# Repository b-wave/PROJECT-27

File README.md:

# PROJECT-27
Which was a Telemetering transmitter from the 1964 era book **103 Simple Transistor Projects**, by Tom Knitel  I grew up with this book and this was one of my bucket-list projects from it. Although I am *not exactly sure* how my pre-teen self planned to send this device aloft.  I do remember trying to build it up with a CB radio crystal and a few random transistors (it never worked) and had some vague idea of 20 or so toy helium balloons in a laundry bag! Informaton from this transmitter is not sent digitally from this device either.  The RF is AM modulated and the frequency of the modulation is controlled by a thermistor.  Of course, this would need to be calibrated to make any sense of the data. 

For more details on my check out my site: (https://brainwave57.blogspot.com/2022/11/project-27-part-1.html)

103 Projects!

I created two versions, MKI and MKIII are functional. The MK1 is pretty much a copy of the original version. The Mk3 may actually be legal to operate as a telemetering device on the current 27-MHz band. The MK3 is a modern version that also features the same simple Temperature-to-Frequency converter it also now includes a way to include altitude information encoded in the length of the tone burst (Pulse modulated) and even a bright LED beacon.  I thought I had some of the original Ge Transistors, but it turned out they were really old-style Si devices. I found sources for the original transistors online but at a cost that did not make it practical to try or even risk these antique transistors to this experiment... Even buying the Over Tone crystals is costly. I did find a solution for both.  

They are built without any Germanium or PNP transistors. 

The files here are "modern" versions of the **#27 Telemetering Transmitter**. Basically, the first version was a simple crystal oscillator and a multivibrator circuit - just like the original. The crystal was taken from a toy "27MHZ" remote controller. It turns out the frequency is in the ISM telemetry part of that band. The original project #27 goes into detail about the FCC requirements, in force in 1964. He even recommends the transmitter is inspected by a certified person to comply with the then requirements. I did a quick search of the FCC rules and found the mentioned sections are not even in existence. I did see the current requirements have differences are that more power is apparently now allowed - but - there is now a limit now on the length of time a "tone" can be transmitted. The original and MK1 transmit continuously so they would definitely not be legal. But of course, none of these transmitters are FCC type accepted for manufacture but for experimental purposes on the ISM band it should be OK.

Telemetering Tranmiter Version MK1 3D View

That's why the new Mk3 version.  It attempts to limit the time that the tone is transmitted and clean up the output to hopefully comply with the rules.  The original seems to rely on low power and the antenna length to limit the spurious emissions surely caused by a 3rd overtone crystal oscillator.  The timing circuit was implemented as another two-transistor multivibrator. Since it originally started life as a "Flashing beacon" in the same book -- I also added a high efficiency LED that produces a bright strobe beacon as well so it can be tracked and possibly help find it.  Since the strobes timing was arbitrarily set, I realized that that could be, in fact, controlled and a second channel of information could be transmitted by this pulse length.  I then constructed a 1960's technology version of an altimeter that is a simple sealed tube of air with a plunger attached to a slide potentiometer. I will add details of this device later. (Mk2 was a never completed high(er) power version)

Telemetering Tranmitter Version MK3 (Top 3D View)

The original was intended to powered only by 1.5V AA cell.  Three volts would actually be OK for FCC power output requirements. I think a modern LiPo would probably survive the extreme cold a balloon-borne sonde would encounter. There is now plenty of room for two cells as shown on the bottom view. Of course, weight is a prime consideration for balloon payloads as well so LiPo may be best.  

Tranmitter Version MK3 (Bottom 3D View)

I doubt if this thing ever did fly on a balloon to or will my version but it was a fun pandemic project just to see it work. 

#Circuit boards are availble on:

MKI  Board: https://oshpark.com/shared_projects/9dS7OwyD

MKII Board:  **Never Finished** 

MKIII Board: https://oshpark.com/shared_projects/CLHAeEab

Cheers!

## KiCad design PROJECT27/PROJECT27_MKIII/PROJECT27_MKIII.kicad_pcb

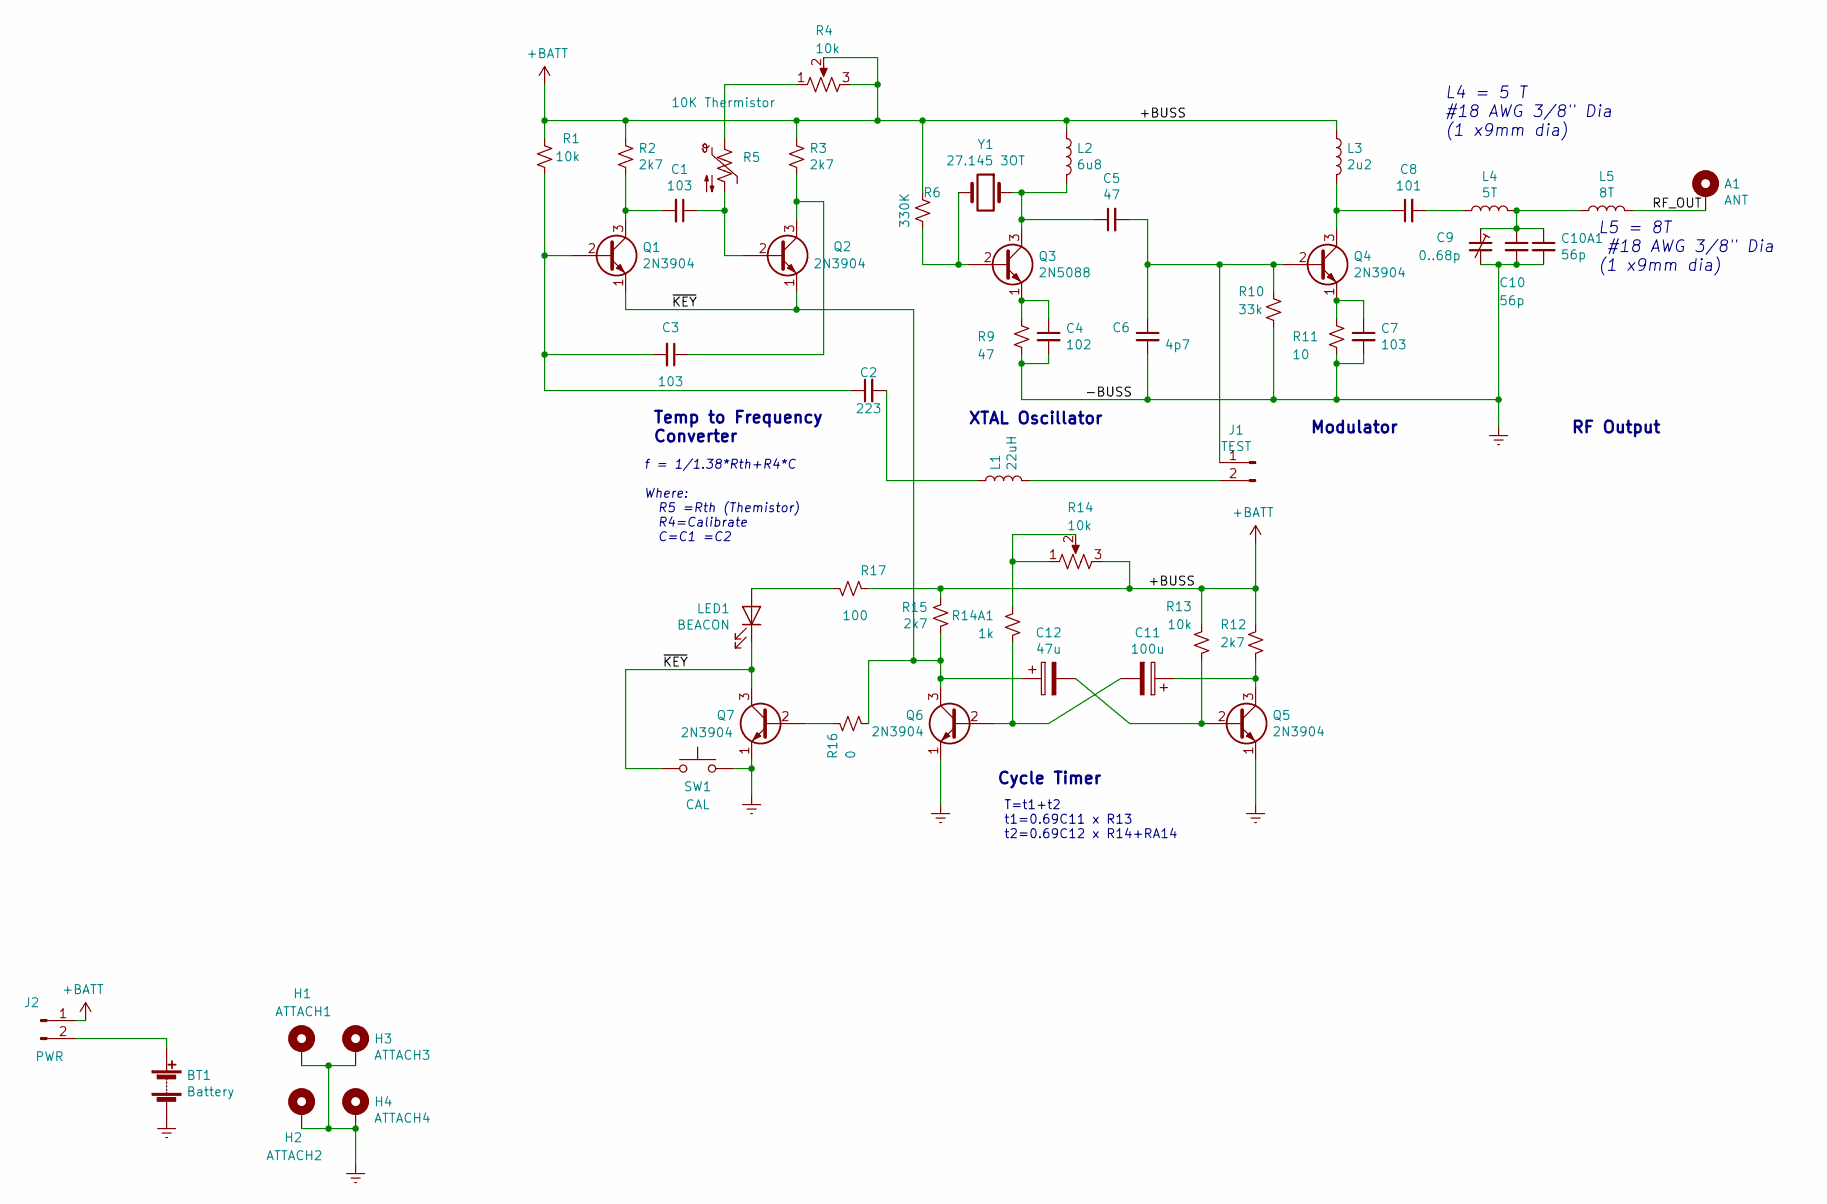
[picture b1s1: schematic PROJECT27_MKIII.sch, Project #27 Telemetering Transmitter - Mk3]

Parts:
A1: ANT; Hole_100_75
BT1: Battery; BatteryHolder_Keystone_2468_2xAAA
C1, C3, C7: 103; C_Disc_D5.0mm_W2.5mm_P2.50mm
C2: 223; C_Disc_D5.0mm_W2.5mm_P2.50mm
C4: 102; C_Disc_D5.0mm_W2.5mm_P2.50mm
C5: 47; C_Disc_D5.0mm_W2.5mm_P2.50mm
C6: 4p7; C_Disc_D5.0mm_W2.5mm_P2.50mm
C8: 101; C_Disc_D5.0mm_W2.5mm_P2.50mm
C9: 0..68p; C_Trimmer_Murata_TZB4-B
C10, C10A1: 56p; C_Disc_D5.0mm_W2.5mm_P2.50mm
C11: 100u; C_Radial_D8.0mm_H11.5mm_P3.50mm
C12: 47u; C_Radial_D5.0mm_H11.0mm_P2.00mm
H1: ATTACH1; MountingHole_2.2mm_M2_Pad_Via
H2: ATTACH2; MountingHole_2.2mm_M2_Pad_Via
H3: ATTACH3; MountingHole_2.2mm_M2_Pad_Via
H4: ATTACH4; MountingHole_2.2mm_M2_Pad_Via
J1: TEST; PinHeader_1x02_P2.54mm_Vertical
J2: PWR; PinHeader_1x02_P2.54mm_Vertical
L1: 22uH; L_Axial_L5.3mm_D2.2mm_P10.16mm_Horizontal_Vishay_IM-1
L2: 6u8; L_Axial_L5.3mm_D2.2mm_P10.16mm_Horizontal_Vishay_IM-1
L3: 2u2; L_Axial_L5.3mm_D2.2mm_P10.16mm_Horizontal_Vishay_IM-1
L4: 5T; L_Axial_L16.0mm_D7.5mm_P7.62mm_Vertical_Fastron_XHBCC
L5: 8T; L_Axial_L16.0mm_D7.5mm_P7.62mm_Vertical_Fastron_XHBCC
LED1: BEACON; LED_D3.0mm
Q1, Q2, Q4, Q5, Q6, Q7: 2N3904; TO-92_Inline
Q3: 2N5088; TO-92_Inline
R1, R13: 10k; R_Axial_DIN0204_L3.6mm_D1.6mm_P7.62mm_Horizontal
R2, R3, R12, R15: 2k7; R_Axial_DIN0204_L3.6mm_D1.6mm_P7.62mm_Horizontal
R4, R14: 10k; Potentiometer_Bourns_3339P_Vertical_HandSoldering
R5: 10K Thermistor; RV_Disc_D7mm_W3.4mm_P5mm
R6: 330K; R_Axial_DIN0204_L3.6mm_D1.6mm_P7.62mm_Horizontal
R9: 47; R_Axial_DIN0204_L3.6mm_D1.6mm_P7.62mm_Horizontal
R10: 33k; R_Axial_DIN0204_L3.6mm_D1.6mm_P7.62mm_Horizontal
R11: 10; R_Axial_DIN0204_L3.6mm_D1.6mm_P7.62mm_Horizontal
R14A1: 1k; R_Axial_DIN0207_L6.3mm_D2.5mm_P2.54mm_Vertical
R16: 0; R_Axial_DIN0204_L3.6mm_D1.6mm_P7.62mm_Horizontal
R17: 100; R_Axial_DIN0204_L3.6mm_D1.6mm_P7.62mm_Horizontal
SW1: CAL; SW_PUSH_6mm_H4.3mm
Y1: 27.145 3OT; Crystal_HC49-U_Horizontal

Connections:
+BATT: J2.1, L2.1, L3.1, R1.2, R2.1, R3.1, R4.2, R4.3, R6.1, R12.2, R13.1, R14.3, R15.1, R17.1
/RF_OUT: A1.1, L5.2
/~KEY: C12.1, LED1.1 (K), Q1.1 (E), Q2.1 (E), Q6.3 (C), Q7.3 (C), R15.2, R16.1, SW1.2
GNDREF: BT1.2 (-), C4.2, C6.2, C7.2, C9.2, C10.2, C10A1.2, H1.1, H2.1, H3.1, H4.1, Q5.1 (E), Q6.1 (E), Q7.1 (E), R9.2, R10.2, R11.2, SW1.1
unnamed: BT1.1 (+), J2.2
unnamed: C1.1, Q2.2 (B), R5.2
unnamed: C1.2, Q1.3 (C), R2.2
unnamed: C2.1, C3.2, Q1.2 (B), R1.1
unnamed: C2.2, L1.1
unnamed: C3.1, Q2.3 (C), R3.2
unnamed: C4.1, Q3.1 (E), R9.1
unnamed: C5.1, L2.2, Q3.3 (C), Y1.1
unnamed: C5.2, C6.1, J1.1, Q4.2 (B), R10.1
unnamed: C7.1, Q4.1 (E), R11.1
unnamed: C8.1, L3.2, Q4.3 (C)
unnamed: C8.2, L4.2
unnamed: C9.1, C10.1, C10A1.1, L4.1, L5.1
unnamed: C11.1, Q5.3 (C), R12.1
unnamed: C11.2, Q6.2 (B), R14A1.2
unnamed: C12.2, Q5.2 (B), R13.2
unnamed: J1.2, L1.2
unnamed: LED1.2 (A), R17.2
unnamed: Q3.2 (B), R6.2, Y1.2
unnamed: Q7.2 (B), R16.2
unnamed: R4.1, R5.1
unnamed: R14.1, R14.2, R14A1.1

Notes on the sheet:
T=t1+t2 t1=0.69C11 x R13 t2=0.69C12 x R14+RA14
f = 1/1.38*Rth+R4*C Where: R5 =Rth (Themistor) R4=Calibrate C=C1 =C2
Cycle Timer
Temp to Frequency Converter
XTAL Oscillator
RF Output
L4 = 5 T #18 AWG 3/8" Dia (1 x9mm dia)
L5 = 8T #18 AWG 3/8" Dia (1 x9mm dia)
Modulator

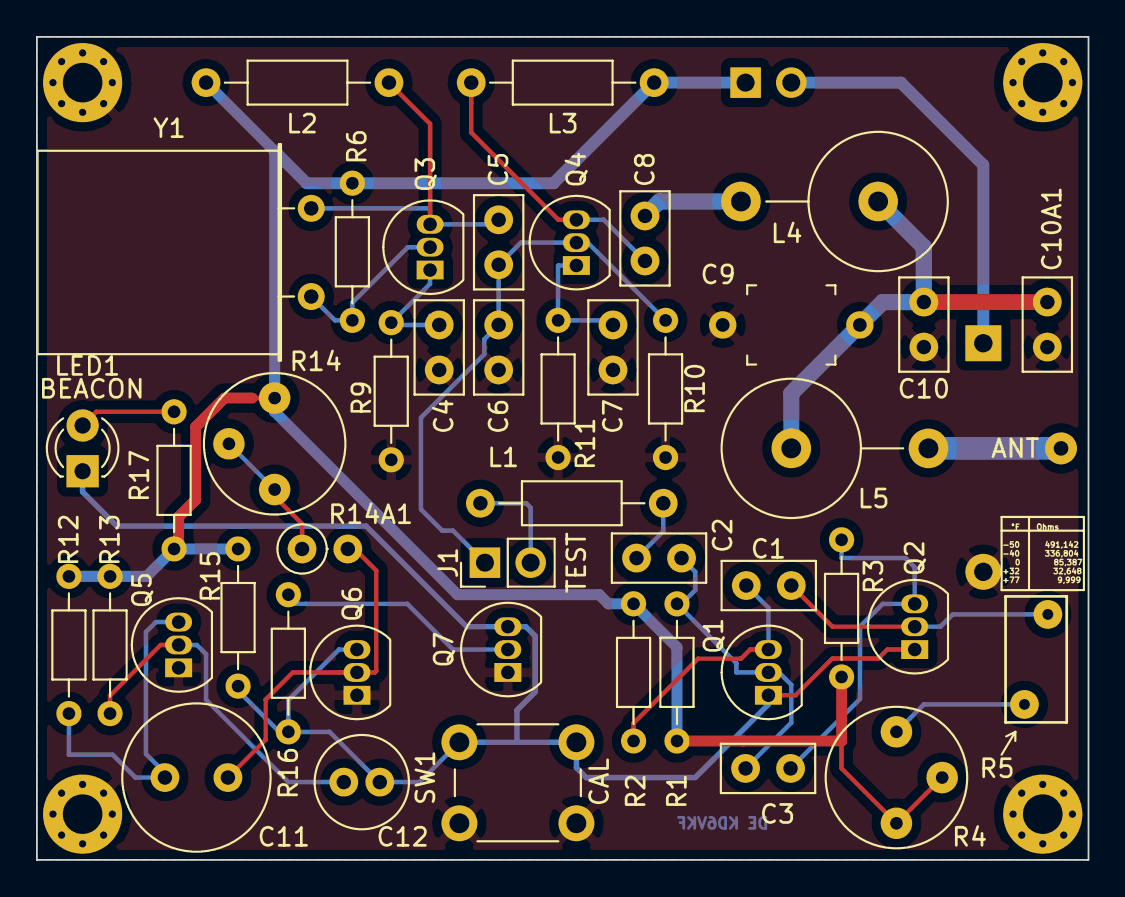
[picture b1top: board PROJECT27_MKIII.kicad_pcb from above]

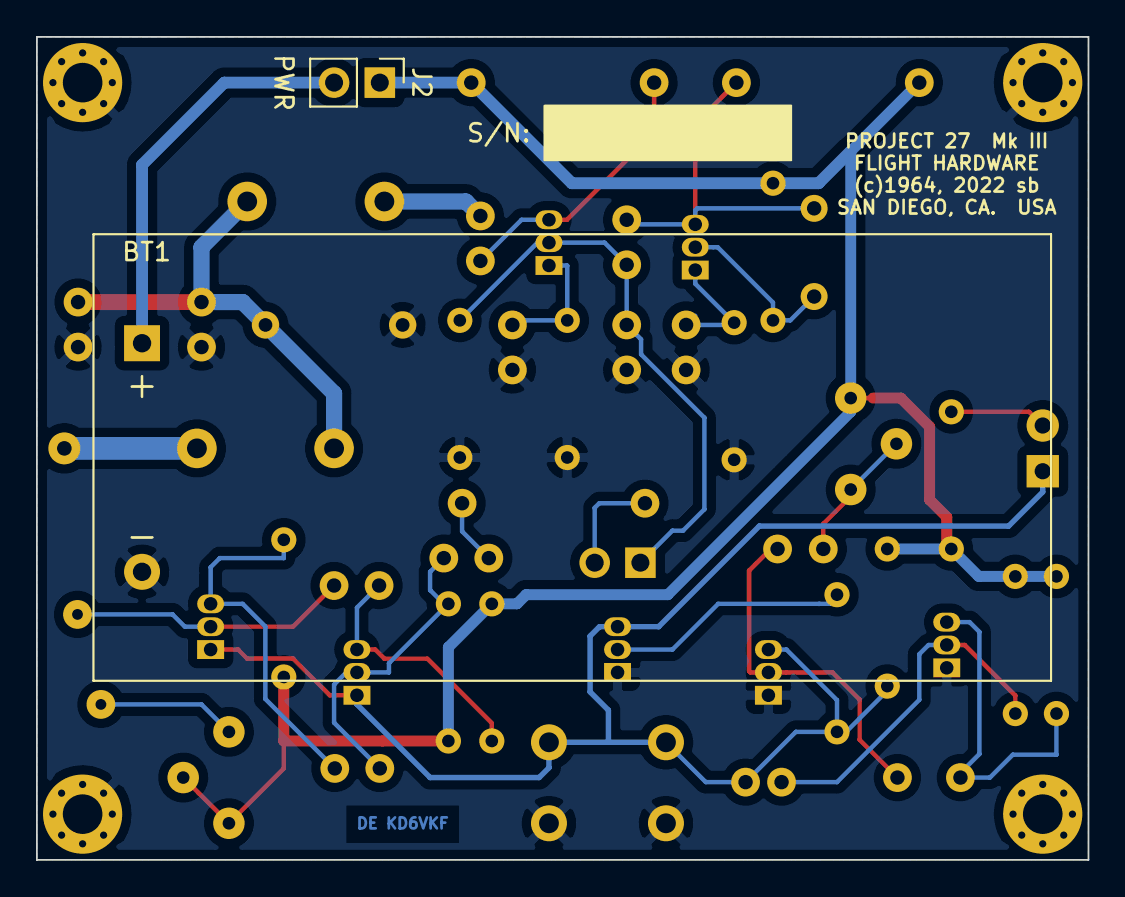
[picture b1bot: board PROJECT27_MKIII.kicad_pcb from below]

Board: 2 copper layers, 58.4 x 45.7 mm, 52 parts (2 on the bottom side), 26 nets.

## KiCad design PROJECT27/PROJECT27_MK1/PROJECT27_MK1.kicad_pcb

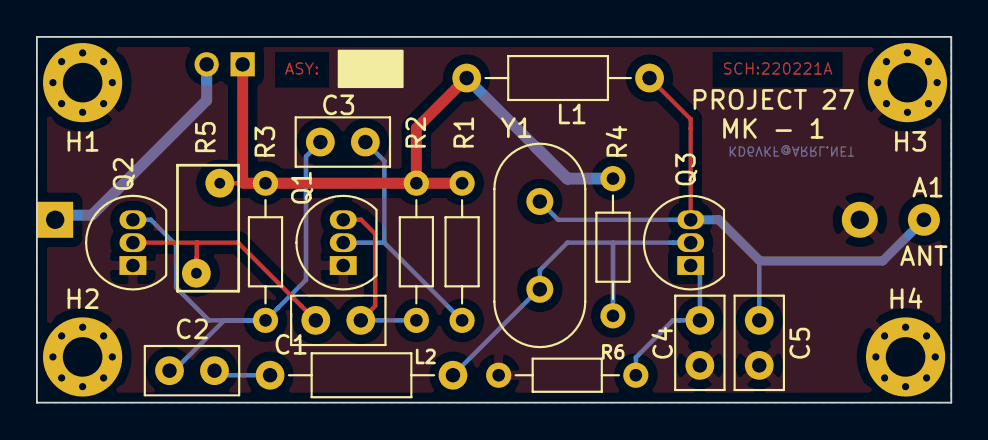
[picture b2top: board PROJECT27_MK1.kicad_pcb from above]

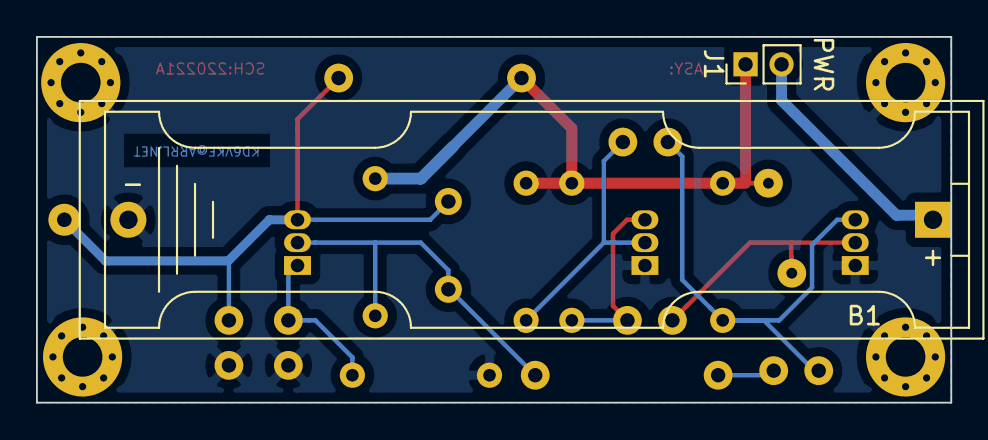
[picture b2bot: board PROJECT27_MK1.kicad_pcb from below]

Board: 2 copper layers, 50.8 x 20.3 mm, 24 parts (2 on the bottom side), 12 nets.

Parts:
A1: ANT; Hole_100_75
B1: 1.5V; BatteryHolder_Keystone_2466_1xAAA
C1, C3: 103; C_Disc_D5.0mm_W2.5mm_P2.50mm
C2: 47; C_Disc_D5.0mm_W2.5mm_P2.50mm
C4: 102; C_Disc_D5.0mm_W2.5mm_P2.50mm
C5: 4p7; C_Disc_D5.0mm_W2.5mm_P2.50mm
H1, H2, H3, H4: ATTACH; MountingHole_2.2mm_M2_Pad_Via
J1: PWR; PinHeader_1x02_P2.00mm_Vertical
L1, L2: 1uH; L_Axial_L5.3mm_D2.2mm_P10.16mm_Horizontal_Vishay_IM-1
Q1, Q2: 2N3904; TO-92_Inline
Q3: 2N5088; TO-92_Inline
R1: 10K; R_Axial_DIN0204_L3.6mm_D1.6mm_P7.62mm_Horizontal
R2, R3: 2k7; R_Axial_DIN0204_L3.6mm_D1.6mm_P7.62mm_Horizontal
R4: 330K; R_Axial_DIN0204_L3.6mm_D1.6mm_P7.62mm_Horizontal
R5: 10K Thermistor; RV_Disc_D7mm_W3.4mm_P5mm
R6: 10; R_Axial_DIN0204_L3.6mm_D1.6mm_P7.62mm_Horizontal
Y1: 27.145 3OT; Crystal_HC49-U_Vertical

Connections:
+BATT: J1.1, L1.1, R1.1, R2.2, R3.1, R4.1, R5.1
GNDREF: B1.2, C4.2, C5.2, H1.1, H2.1, H3.1, H4.1, Q1.1, Q2.1, R6.2
unnamed: A1.1, C5.1, L1.2
unnamed: B1.1, J1.2
unnamed: C1.1, Q2.2, R5.2
unnamed: C1.2, Q1.3, R2.1
unnamed: C2.1, C3.1, Q2.3, R3.2
unnamed: C2.2, L2.1
unnamed: C3.2, Q1.2, R1.2
unnamed: C4.1, Q3.1, R6.1
unnamed: L2.2, Q3.2, R4.2, Y1.2
unnamed: Q3.3, Y1.1

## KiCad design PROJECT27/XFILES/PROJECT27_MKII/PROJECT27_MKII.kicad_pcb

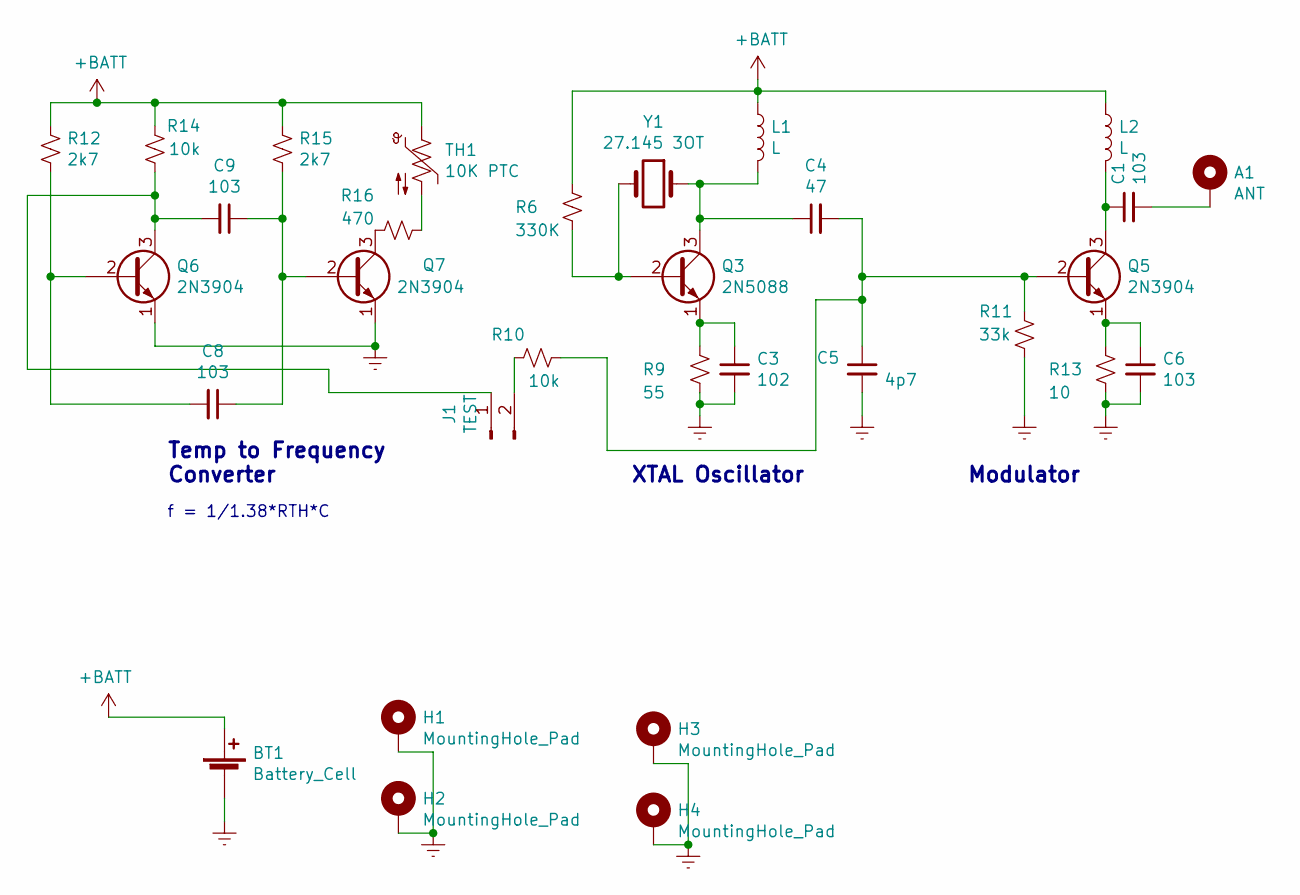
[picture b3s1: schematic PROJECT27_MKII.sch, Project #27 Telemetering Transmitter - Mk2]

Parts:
A1: ANT; Hole_100_75
BT1: Battery_Cell; BatteryHolder_Keystone_2466_1xAAA
C1, C6, C8, C9: 103; C_Disc_D5.0mm_W2.5mm_P2.50mm
C3: 102; C_Disc_D5.0mm_W2.5mm_P2.50mm
C4: 47; C_Disc_D5.0mm_W2.5mm_P2.50mm
C5: 4p7; C_Disc_D5.0mm_W2.5mm_P2.50mm
H1, H2, H3, H4: MountingHole_Pad; MountingHole_2.2mm_M2_Pad_Via
J1: TEST; PinHeader_1x02_P2.54mm_Vertical
L1, L2: L; L_Axial_L5.3mm_D2.2mm_P10.16mm_Horizontal_Vishay_IM-1
Q3: 2N5088; TO-92_Inline
Q5, Q6, Q7: 2N3904; TO-92_Inline
R6: 330K; R_Axial_DIN0204_L3.6mm_D1.6mm_P7.62mm_Horizontal
R9: 55; R_Axial_DIN0204_L3.6mm_D1.6mm_P7.62mm_Horizontal
R10: 10k; R_Axial_DIN0207_L6.3mm_D2.5mm_P2.54mm_Vertical
R11: 33k; R_Axial_DIN0204_L3.6mm_D1.6mm_P7.62mm_Horizontal
R12, R15: 2k7; R_Axial_DIN0204_L3.6mm_D1.6mm_P7.62mm_Horizontal
R13: 10; R_Axial_DIN0204_L3.6mm_D1.6mm_P7.62mm_Horizontal
R14: 10k; R_Axial_DIN0204_L3.6mm_D1.6mm_P7.62mm_Horizontal
R16: 470; R_Axial_DIN0204_L3.6mm_D1.6mm_P7.62mm_Horizontal
TH1: 10K PTC; RV_Disc_D7mm_W3.4mm_P5mm
Y1: 27.145 3OT; Crystal_HC49-U_Vertical

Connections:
+BATT: BT1.1 (+), L1.1, L2.1, R6.1, R12.1, R14.2, R15.1, TH1.1
GNDREF: BT1.2 (-), C3.2, C5.2, C6.2, H1.1, H2.1, H3.1, H4.1, Q6.1 (E), Q7.1 (E), R9.2, R11.2, R13.2
unnamed: A1.1, C1.2
unnamed: C1.1, L2.2, Q5.3 (C)
unnamed: C3.1, Q3.1 (E), R9.1
unnamed: C4.1, L1.2, Q3.3 (C), Y1.1
unnamed: C4.2, C5.1, Q5.2 (B), R10.2, R11.1
unnamed: C6.1, Q5.1 (E), R13.1
unnamed: C8.1, C9.1, Q7.2 (B), R15.2
unnamed: C8.2, Q6.2 (B), R12.2
unnamed: C9.2, J1.1, Q6.3 (C), R14.1
unnamed: J1.2, R10.1
unnamed: Q3.2 (B), R6.2, Y1.2
unnamed: Q7.3 (C), R16.1
unnamed: R16.2, TH1.2

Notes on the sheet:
f = 1/1.38*RTH*C
Temp to Frequency Converter
XTAL Oscillator
Modulator

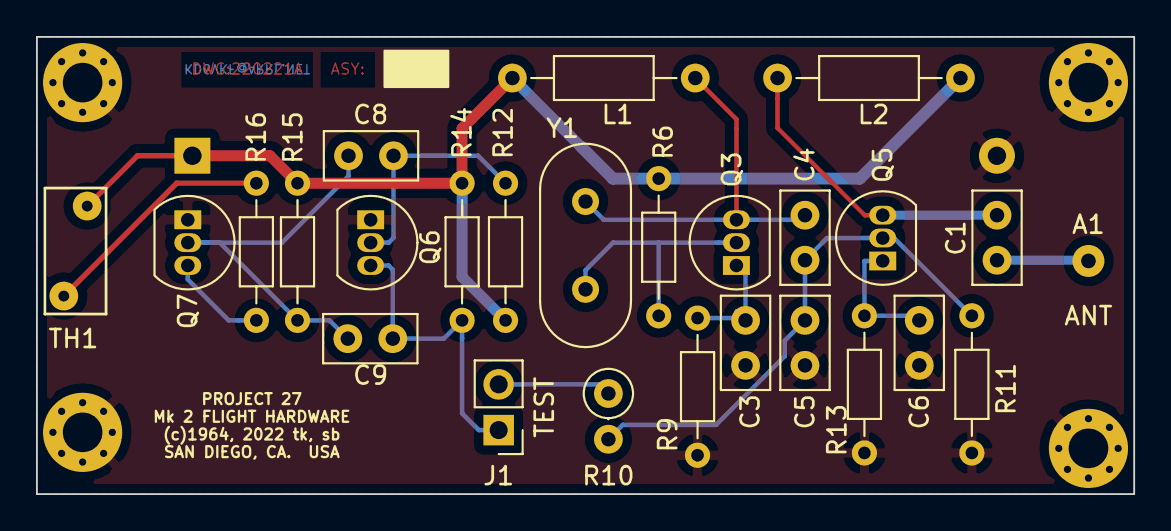
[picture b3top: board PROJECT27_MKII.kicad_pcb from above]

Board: 2 copper layers, 61.0 x 25.4 mm, 31 parts (1 on the bottom side), 15 nets.

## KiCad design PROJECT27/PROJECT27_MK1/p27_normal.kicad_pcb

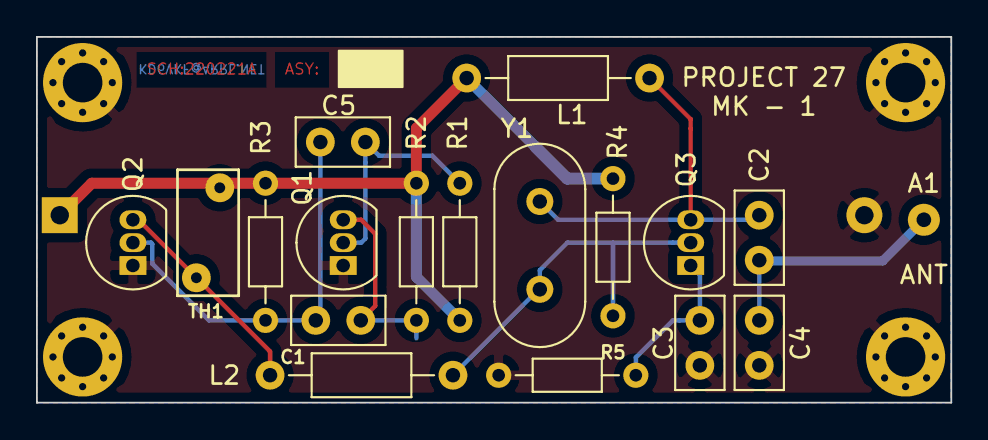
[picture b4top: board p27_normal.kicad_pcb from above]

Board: 2 copper layers, 50.8 x 20.3 mm, 23 parts (1 on the bottom side), 10 nets.

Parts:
A1: ANT; Hole_100_75
BT1: Battery_Cell; BatteryHolder_Keystone_2466_1xAAA
C1, C5: 103; C_Disc_D5.0mm_W2.5mm_P2.50mm
C2: 47; C_Disc_D5.0mm_W2.5mm_P2.50mm
C3: 102; C_Disc_D5.0mm_W2.5mm_P2.50mm
C4: 4p7; C_Disc_D5.0mm_W2.5mm_P2.50mm
H1, H2, H3, H4: MountingHole_Pad; MountingHole_2.2mm_M2_Pad_Via
L1, L2: 1uH; L_Axial_L5.3mm_D2.2mm_P10.16mm_Horizontal_Vishay_IM-1
Q1, Q2: 2N3904; TO-92_Inline
Q3: 2N5088; TO-92_Inline
R1, R3: 2k7; R_Axial_DIN0204_L3.6mm_D1.6mm_P7.62mm_Horizontal
R2: 10k; R_Axial_DIN0204_L3.6mm_D1.6mm_P7.62mm_Horizontal
R4: 330K; R_Axial_DIN0204_L3.6mm_D1.6mm_P7.62mm_Horizontal
R5: 55; R_Axial_DIN0204_L3.6mm_D1.6mm_P7.62mm_Horizontal
TH1: 10K PTC; RV_Disc_D7mm_W3.4mm_P5mm
Y1: 27.145 3OT; Crystal_HC49-U_Vertical

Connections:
+BATT: BT1.1, L1.1, R1.1, R2.2, R3.1, R4.1, TH1.1
GNDREF: BT1.2, C3.2, C4.2, H1.1, H2.1, H3.1, H4.1, Q1.1, Q2.1, R5.2
unnamed: A1.1, C2.2, C4.1
unnamed: C1.1, C5.1, Q2.2, R3.2
unnamed: C1.2, Q1.3, R2.1
unnamed: C2.1, L1.2, Q3.3, Y1.1
unnamed: C3.1, Q3.1, R5.1
unnamed: C5.2, Q1.2, R1.2
unnamed: L2.1, Q2.3, TH1.2
unnamed: L2.2, Q3.2, R4.2, Y1.2

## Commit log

2022-11-09 Add files via upload
    More BMP files from Blog
2022-11-09 Delete PROJECT27 directory
    clean up directory
2022-11-09 Add files via upload
    to clean up directory
2022-11-09 Add files via upload
    Clean up extra files
2022-11-10 Update README.md
    added blog link
2023-02-15 Update README.md
    added OSH Park url for Circuit boards
2023-02-15 Update README.md
    OSH Park Board files

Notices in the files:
PROJECT27/PROJECT27_MKIII/PROJECT27_MKIII.kicad_pcb:
(c)1964, 2022 sb
PROJECT27/PROJECT27_MKIII/PROJECT27_MKIII.sch:
(c) 1964 Jon F. Rider, Hayden Book, Co, Inc
PROJECT27/XFILES/PROJECT27_MKII/PROJECT27_MKII.kicad_pcb:
(c)1964, 2022 tk, sb
